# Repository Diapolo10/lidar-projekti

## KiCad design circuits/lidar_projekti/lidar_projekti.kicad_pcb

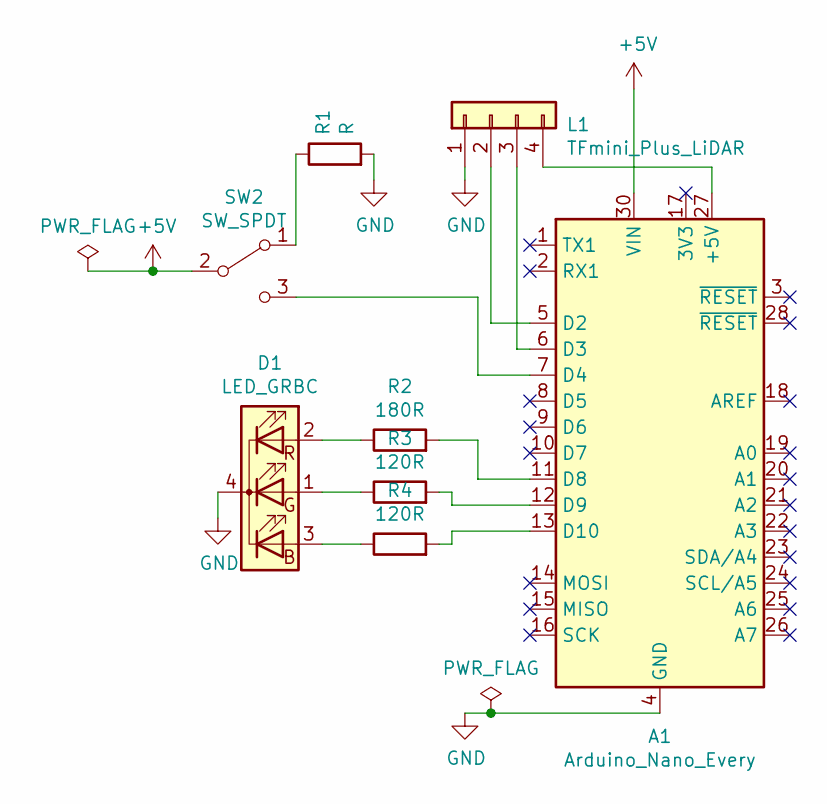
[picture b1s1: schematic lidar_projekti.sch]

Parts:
A1: Arduino_Nano_Every; Arduino_Nano
D1: LED_GRBC; LED_ASMB-KTF0-0A306
L1: TFmini_Plus_LiDAR; FanPinHeader_1x04_P2.54mm_Vertical
R1: R; R_Axial_DIN0309_L9.0mm_D3.2mm_P12.70mm_Horizontal
R2: 180R; R_Axial_DIN0309_L9.0mm_D3.2mm_P12.70mm_Horizontal
R3, R4: 120R; R_Axial_DIN0309_L9.0mm_D3.2mm_P12.70mm_Horizontal
SW2: SW_SPDT; SW_SPST_B3S-1100

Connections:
+5V: A1.30 (VIN), SW2.2 (B)
GND: A1.4 (GND), A1.29 (GND), D1.4 (K), L1.1, R1.2
unnamed: A1.5 (D2), L1.2
unnamed: A1.6 (D3), L1.3
unnamed: A1.7 (D4), SW2.3 (C)
unnamed: A1.11 (D8), R2.2
unnamed: A1.12 (D9), R3.2
unnamed: A1.13 (D10), R4.2
unnamed: A1.27 (+5V), L1.4
unnamed: D1.1 (GA), R3.1
unnamed: D1.2 (RA), R2.1
unnamed: D1.3 (BA), R4.1
unnamed: R1.1, SW2.1 (A)

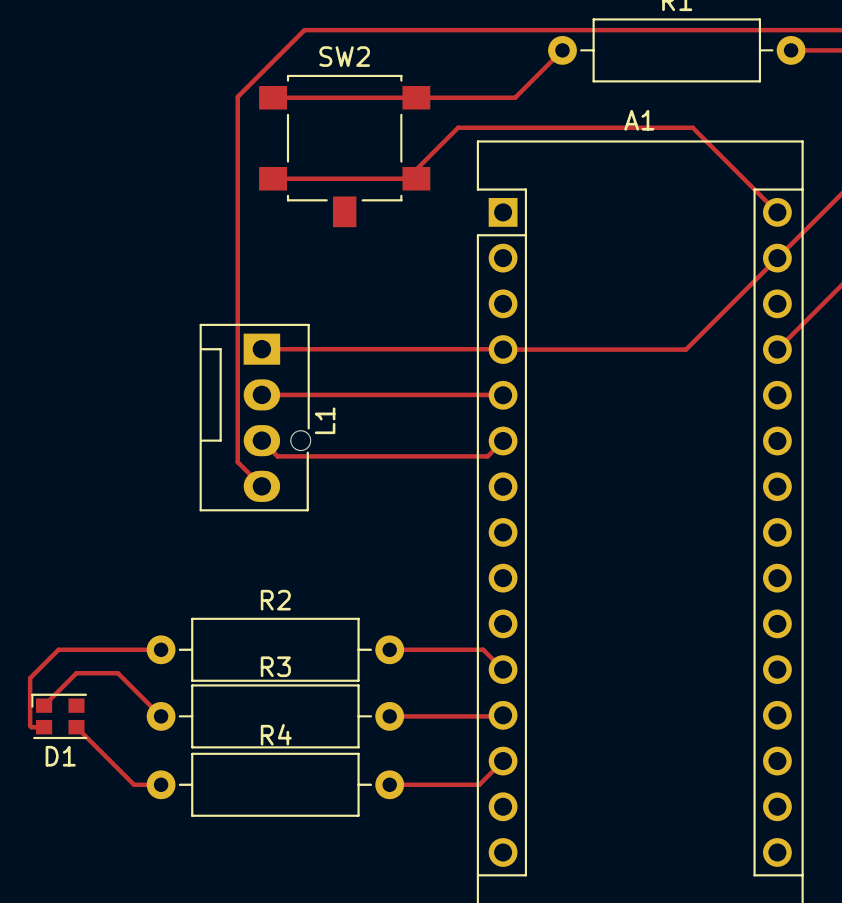
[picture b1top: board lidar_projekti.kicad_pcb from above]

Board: 2 copper layers, 8 parts (0 on the bottom side), 13 nets.

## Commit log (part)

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2021-10-27 Add LICENSE
2021-10-27 Add CHANGELOG.md
2021-10-27 Added Code of Conduct
2021-10-27 [PATCH] Added TFMPlus
2021-11-16 [PATCH] Added prototype project
2021-11-30 [PATCH] Testing integrations
2021-11-30 [PATCH] Added Doxygen comments for testing
2021-12-01 [PATCH] Fixed Doxygen
2021-12-07 [PATCH] Fixes
2021-12-07 [PATCH] Even more fixes
2021-12-07 [PATCH] Added functionality, excluding voltage
2021-12-08 [PATCH] Last-minute test
2021-12-08 [PATCH] Hopefully fixed docs
2021-12-08 [PATCH] Implemented sensor unit mode switching
2021-12-08 [PATCH] More docs
2021-12-09 [PATCH] Fixed builds and added more docs
2021-12-10 [PATCH] Updated README.rst
2021-12-10 [PATCH] Fixed links
2021-12-15 [PATCH] Added pinMode inits just in case
2021-12-15 [PATCH] Fixed battery voltage pin
2021-12-15 [PATCH] Updated ports
2021-12-15 [PATCH] Set correct button state
2022-03-15 [PATCH] Updated KiCAD files
2022-03-15 [PATCH] Added PCB schematics
2022-03-15 [PATCH] Screenshots
2023-02-21 Bump dependabot/fetch-metadata from 1.3.1 to 1.3.6
    Bumps [dependabot/fetch-metadata](https://github.com/dependabot/fetch-metadata) from 1.3.1 to 1.3.6.
    - [Release notes](https://github.com/dependabot/fetch-metadata/releases)
    - [Commits](https://github.com/dependabot/fetch-metadata/compare/v1.3.1...v1.3.6)
    ---
    updated-dependencies:
    - dependency-name: dependabot/fetch-metadata
2023-02-25 Bump actions/checkout from 2 to 3
    Bumps [actions/checkout](https://github.com/actions/checkout) from 2 to 3.
    - [Release notes](https://github.com/actions/checkout/releases)
    - [Changelog](https://github.com/actions/checkout/blob/main/CHANGELOG.md)
    - [Commits](https://github.com/actions/checkout/compare/v2...v3)
    ---
    updated-dependencies:
2023-03-01 Bump breathe from 4.34.0 to 4.35.0
    Bumps [breathe](https://github.com/michaeljones/breathe) from 4.34.0 to 4.35.0.
    - [Release notes](https://github.com/michaeljones/breathe/releases)
    - [Changelog](https://github.com/breathe-doc/breathe/blob/main/CHANGELOG.rst)
    - [Commits](https://github.com/michaeljones/breathe/compare/v4.34.0...v4.35.0)
    ---
    updated-dependencies:
2023-04-18 Bump dependabot/fetch-metadata from 1.3.6 to 1.4.0
    Bumps [dependabot/fetch-metadata](https://github.com/dependabot/fetch-metadata) from 1.3.6 to 1.4.0.
    - [Release notes](https://github.com/dependabot/fetch-metadata/releases)
    - [Commits](https://github.com/dependabot/fetch-metadata/compare/v1.3.6...v1.4.0)
    ---
    updated-dependencies:
    - dependency-name: dependabot/fetch-metadata
2023-04-25 Bump sphinx from 6.1.3 to 6.2.0
    Bumps [sphinx](https://github.com/sphinx-doc/sphinx) from 6.1.3 to 6.2.0.
    - [Release notes](https://github.com/sphinx-doc/sphinx/releases)
    - [Changelog](https://github.com/sphinx-doc/sphinx/blob/master/CHANGES)
    - [Commits](https://github.com/sphinx-doc/sphinx/compare/v6.1.3...v6.2.0)
    ---
    updated-dependencies:
2023-05-02 Bump sphinx from 6.2.1 to 7.0.0
    Bumps [sphinx](https://github.com/sphinx-doc/sphinx) from 6.2.1 to 7.0.0.
    - [Release notes](https://github.com/sphinx-doc/sphinx/releases)
    - [Changelog](https://github.com/sphinx-doc/sphinx/blob/master/CHANGES)
    - [Commits](https://github.com/sphinx-doc/sphinx/compare/v6.2.1...v7.0.0)
    ---
    updated-dependencies:
2023-05-23 Bump dependabot/fetch-metadata from 1.4.0 to 1.5.0
    Bumps [dependabot/fetch-metadata](https://github.com/dependabot/fetch-metadata) from 1.4.0 to 1.5.0.
    - [Release notes](https://github.com/dependabot/fetch-metadata/releases)
    - [Commits](https://github.com/dependabot/fetch-metadata/compare/v1.4.0...v1.5.0)
    ---
    updated-dependencies:
    - dependency-name: dependabot/fetch-metadata
2023-05-25 Bump dependabot/fetch-metadata from 1.5.0 to 1.5.1
    Bumps [dependabot/fetch-metadata](https://github.com/dependabot/fetch-metadata) from 1.5.0 to 1.5.1.
    - [Release notes](https://github.com/dependabot/fetch-metadata/releases)
    - [Commits](https://github.com/dependabot/fetch-metadata/compare/v1.5.0...v1.5.1)
    ---
    updated-dependencies:
    - dependency-name: dependabot/fetch-metadata
2023-07-20 Bump pygments from 2.14.0 to 2.15.0
    Bumps [pygments](https://github.com/pygments/pygments) from 2.14.0 to 2.15.0.
    - [Release notes](https://github.com/pygments/pygments/releases)
    - [Changelog](https://github.com/pygments/pygments/blob/master/CHANGES)
    - [Commits](https://github.com/pygments/pygments/compare/2.14.0...2.15.0)
    ---
    updated-dependencies:
2023-07-27 Bump sphinx from 7.1.0 to 7.1.1
    Bumps [sphinx](https://github.com/sphinx-doc/sphinx) from 7.1.0 to 7.1.1.
    - [Release notes](https://github.com/sphinx-doc/sphinx/releases)
    - [Changelog](https://github.com/sphinx-doc/sphinx/blob/master/CHANGES)
    - [Commits](https://github.com/sphinx-doc/sphinx/compare/v7.1.0...v7.1.1)
    ---
    updated-dependencies:
2023-09-04 Bump actions/checkout from 3 to 4
    Bumps [actions/checkout](https://github.com/actions/checkout) from 3 to 4.
    - [Release notes](https://github.com/actions/checkout/releases)
    - [Changelog](https://github.com/actions/checkout/blob/main/CHANGELOG.md)
    - [Commits](https://github.com/actions/checkout/compare/v3...v4)
    ---
    updated-dependencies:
2023-10-03 Bump urllib3 from 1.26.14 to 1.26.17
    Bumps [urllib3](https://github.com/urllib3/urllib3) from 1.26.14 to 1.26.17.
    - [Release notes](https://github.com/urllib3/urllib3/releases)
    - [Changelog](https://github.com/urllib3/urllib3/blob/main/CHANGES.rst)
    - [Commits](https://github.com/urllib3/urllib3/compare/1.26.14...1.26.17)
    ---
    updated-dependencies:
2023-12-13 Bump github/codeql-action from 2 to 3
    Bumps [github/codeql-action](https://github.com/github/codeql-action) from 2 to 3.
    - [Release notes](https://github.com/github/codeql-action/releases)
    - [Changelog](https://github.com/github/codeql-action/blob/main/CHANGELOG.md)
    - [Commits](https://github.com/github/codeql-action/compare/v2...v3)
    ---
    updated-dependencies:
2024-01-11 Bump jinja2 from 3.1.2 to 3.1.3
    Bumps [jinja2](https://github.com/pallets/jinja) from 3.1.2 to 3.1.3.
    - [Release notes](https://github.com/pallets/jinja/releases)
    - [Changelog](https://github.com/pallets/jinja/blob/main/CHANGES.rst)
    - [Commits](https://github.com/pallets/jinja/compare/3.1.2...3.1.3)
    ---
    updated-dependencies:
2024-04-12 Bump idna from 3.4 to 3.7
    Bumps [idna](https://github.com/kjd/idna) from 3.4 to 3.7.
    - [Release notes](https://github.com/kjd/idna/releases)
    - [Changelog](https://github.com/kjd/idna/blob/master/HISTORY.rst)
    - [Commits](https://github.com/kjd/idna/compare/v3.4...v3.7)
    ---
    updated-dependencies:
2024-05-06 Bump jinja2 from 3.1.3 to 3.1.4
    Bumps [jinja2](https://github.com/pallets/jinja) from 3.1.3 to 3.1.4.
    - [Release notes](https://github.com/pallets/jinja/releases)
    - [Changelog](https://github.com/pallets/jinja/blob/main/CHANGES.rst)
    - [Commits](https://github.com/pallets/jinja/compare/3.1.3...3.1.4)
    ---
    updated-dependencies:
2024-06-18 Bump urllib3 from 1.26.18 to 1.26.19
    Bumps [urllib3](https://github.com/urllib3/urllib3) from 1.26.18 to 1.26.19.
    - [Release notes](https://github.com/urllib3/urllib3/releases)
    - [Changelog](https://github.com/urllib3/urllib3/blob/1.26.19/CHANGES.rst)
    - [Commits](https://github.com/urllib3/urllib3/compare/1.26.18...1.26.19)
    ---
    updated-dependencies:
2024-07-06 Bump certifi from 2023.7.22 to 2024.7.4
    Bumps [certifi](https://github.com/certifi/python-certifi) from 2023.7.22 to 2024.7.4.
    - [Commits](https://github.com/certifi/python-certifi/compare/2023.07.22...2024.07.04)
    ---
    updated-dependencies:
    - dependency-name: certifi
    dependency-type: indirect
2025-01-04 Bump jinja2 from 3.1.4 to 3.1.5
    Bumps [jinja2](https://github.com/pallets/jinja) from 3.1.4 to 3.1.5.
    - [Release notes](https://github.com/pallets/jinja/releases)
    - [Changelog](https://github.com/pallets/jinja/blob/main/CHANGES.rst)
    - [Commits](https://github.com/pallets/jinja/compare/3.1.4...3.1.5)
    ---
    updated-dependencies:
2025-03-12 [PATCH] Update dependencies
2025-06-10 Bump requests from 2.32.3 to 2.32.4 in the pip group
    Bumps the pip group with 1 update: [requests](https://github.com/psf/requests).
    Updates `requests` from 2.32.3 to 2.32.4
    - [Release notes](https://github.com/psf/requests/releases)
    - [Changelog](https://github.com/psf/requests/blob/main/HISTORY.md)
    - [Commits](https://github.com/psf/requests/compare/v2.32.3...v2.32.4)
    ---
2025-08-12 Bump actions/checkout from 4 to 5
    Bumps [actions/checkout](https://github.com/actions/checkout) from 4 to 5.
    - [Release notes](https://github.com/actions/checkout/releases)
    - [Changelog](https://github.com/actions/checkout/blob/main/CHANGELOG.md)
    - [Commits](https://github.com/actions/checkout/compare/v4...v5)
    ---
    updated-dependencies:
2025-11-20 Bump actions/checkout from 5 to 6
    Bumps [actions/checkout](https://github.com/actions/checkout) from 5 to 6.
    - [Release notes](https://github.com/actions/checkout/releases)
    - [Changelog](https://github.com/actions/checkout/blob/main/CHANGELOG.md)
    - [Commits](https://github.com/actions/checkout/compare/v5...v6)
    ---
    updated-dependencies:
2025-12-02 Bump sphinx from 8.2.3 to 9.0.1
    Bumps [sphinx](https://github.com/sphinx-doc/sphinx) from 8.2.3 to 9.0.1.
    - [Release notes](https://github.com/sphinx-doc/sphinx/releases)
    - [Changelog](https://github.com/sphinx-doc/sphinx/blob/master/CHANGES.rst)
    - [Commits](https://github.com/sphinx-doc/sphinx/compare/v8.2.3...v9.0.1)
    ---
    updated-dependencies:
2025-12-04 Bump sphinx from 9.0.2 to 9.0.4
    Bumps [sphinx](https://github.com/sphinx-doc/sphinx) from 9.0.2 to 9.0.4.
    - [Release notes](https://github.com/sphinx-doc/sphinx/releases)
    - [Changelog](https://github.com/sphinx-doc/sphinx/blob/master/CHANGES.rst)
    - [Commits](https://github.com/sphinx-doc/sphinx/compare/v9.0.2...v9.0.4)
    ---
    updated-dependencies:
2026-01-05 Bump dependabot/fetch-metadata from 2.4.0 to 2.5.0
    Bumps [dependabot/fetch-metadata](https://github.com/dependabot/fetch-metadata) from 2.4.0 to 2.5.0.
    - [Release notes](https://github.com/dependabot/fetch-metadata/releases)
    - [Commits](https://github.com/dependabot/fetch-metadata/compare/v2.4.0...v2.5.0)
    ---
    updated-dependencies:
    - dependency-name: dependabot/fetch-metadata
2026-03-26 Bump requests from 2.32.4 to 2.33.0 in the pip group across 1 directory
    Bumps the pip group with 1 update in the / directory: [requests](https://github.com/psf/requests).
    Updates `requests` from 2.32.4 to 2.33.0
    - [Release notes](https://github.com/psf/requests/releases)
    - [Changelog](https://github.com/psf/requests/blob/main/HISTORY.md)
    - [Commits](https://github.com/psf/requests/compare/v2.32.4...v2.33.0)
    ---
2026-04-21 Bump dependabot/fetch-metadata from 3.0.0 to 3.1.0
    Bumps [dependabot/fetch-metadata](https://github.com/dependabot/fetch-metadata) from 3.0.0 to 3.1.0.
    - [Release notes](https://github.com/dependabot/fetch-metadata/releases)
    - [Commits](https://github.com/dependabot/fetch-metadata/compare/v3.0.0...v3.1.0)
    ---
    updated-dependencies:
    - dependency-name: dependabot/fetch-metadata
2026-05-19 Bump idna from 3.10 to 3.15 in the pip group across 1 directory
    Bumps the pip group with 1 update in the / directory: [idna](https://github.com/kjd/idna).
    Updates `idna` from 3.10 to 3.15
    - [Release notes](https://github.com/kjd/idna/releases)
    - [Changelog](https://github.com/kjd/idna/blob/master/HISTORY.md)
    - [Commits](https://github.com/kjd/idna/compare/v3.10...v3.15)
    ---
